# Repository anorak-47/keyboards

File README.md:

# keyboards
Handmade computer keyboards

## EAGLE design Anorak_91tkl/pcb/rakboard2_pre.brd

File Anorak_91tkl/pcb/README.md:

### The 91tkl: Another TKL keyboard PCB

A ten-key-less keyboard with ISO layout and three extra keys.

µCPU: AT90USB646 @ 16MHz

LED controller: 2x ISSI IS31FL3733

#### Notes for rev 2

Place diodes for keys "backspace" and "prtsc" on bottom of PCB

Use capacitors with a diameter below 4.5mm for C27, C26, C5, especially when putting them on the top side of the PCB.

The blue cathode pin of the LED for the key "pause" is not connected to anything. Connect it to the blue cathode pin of the LED for the key "scroll lock". 

#### Note: Out-of-the-box at90usb works only with external 8MHz crystal!

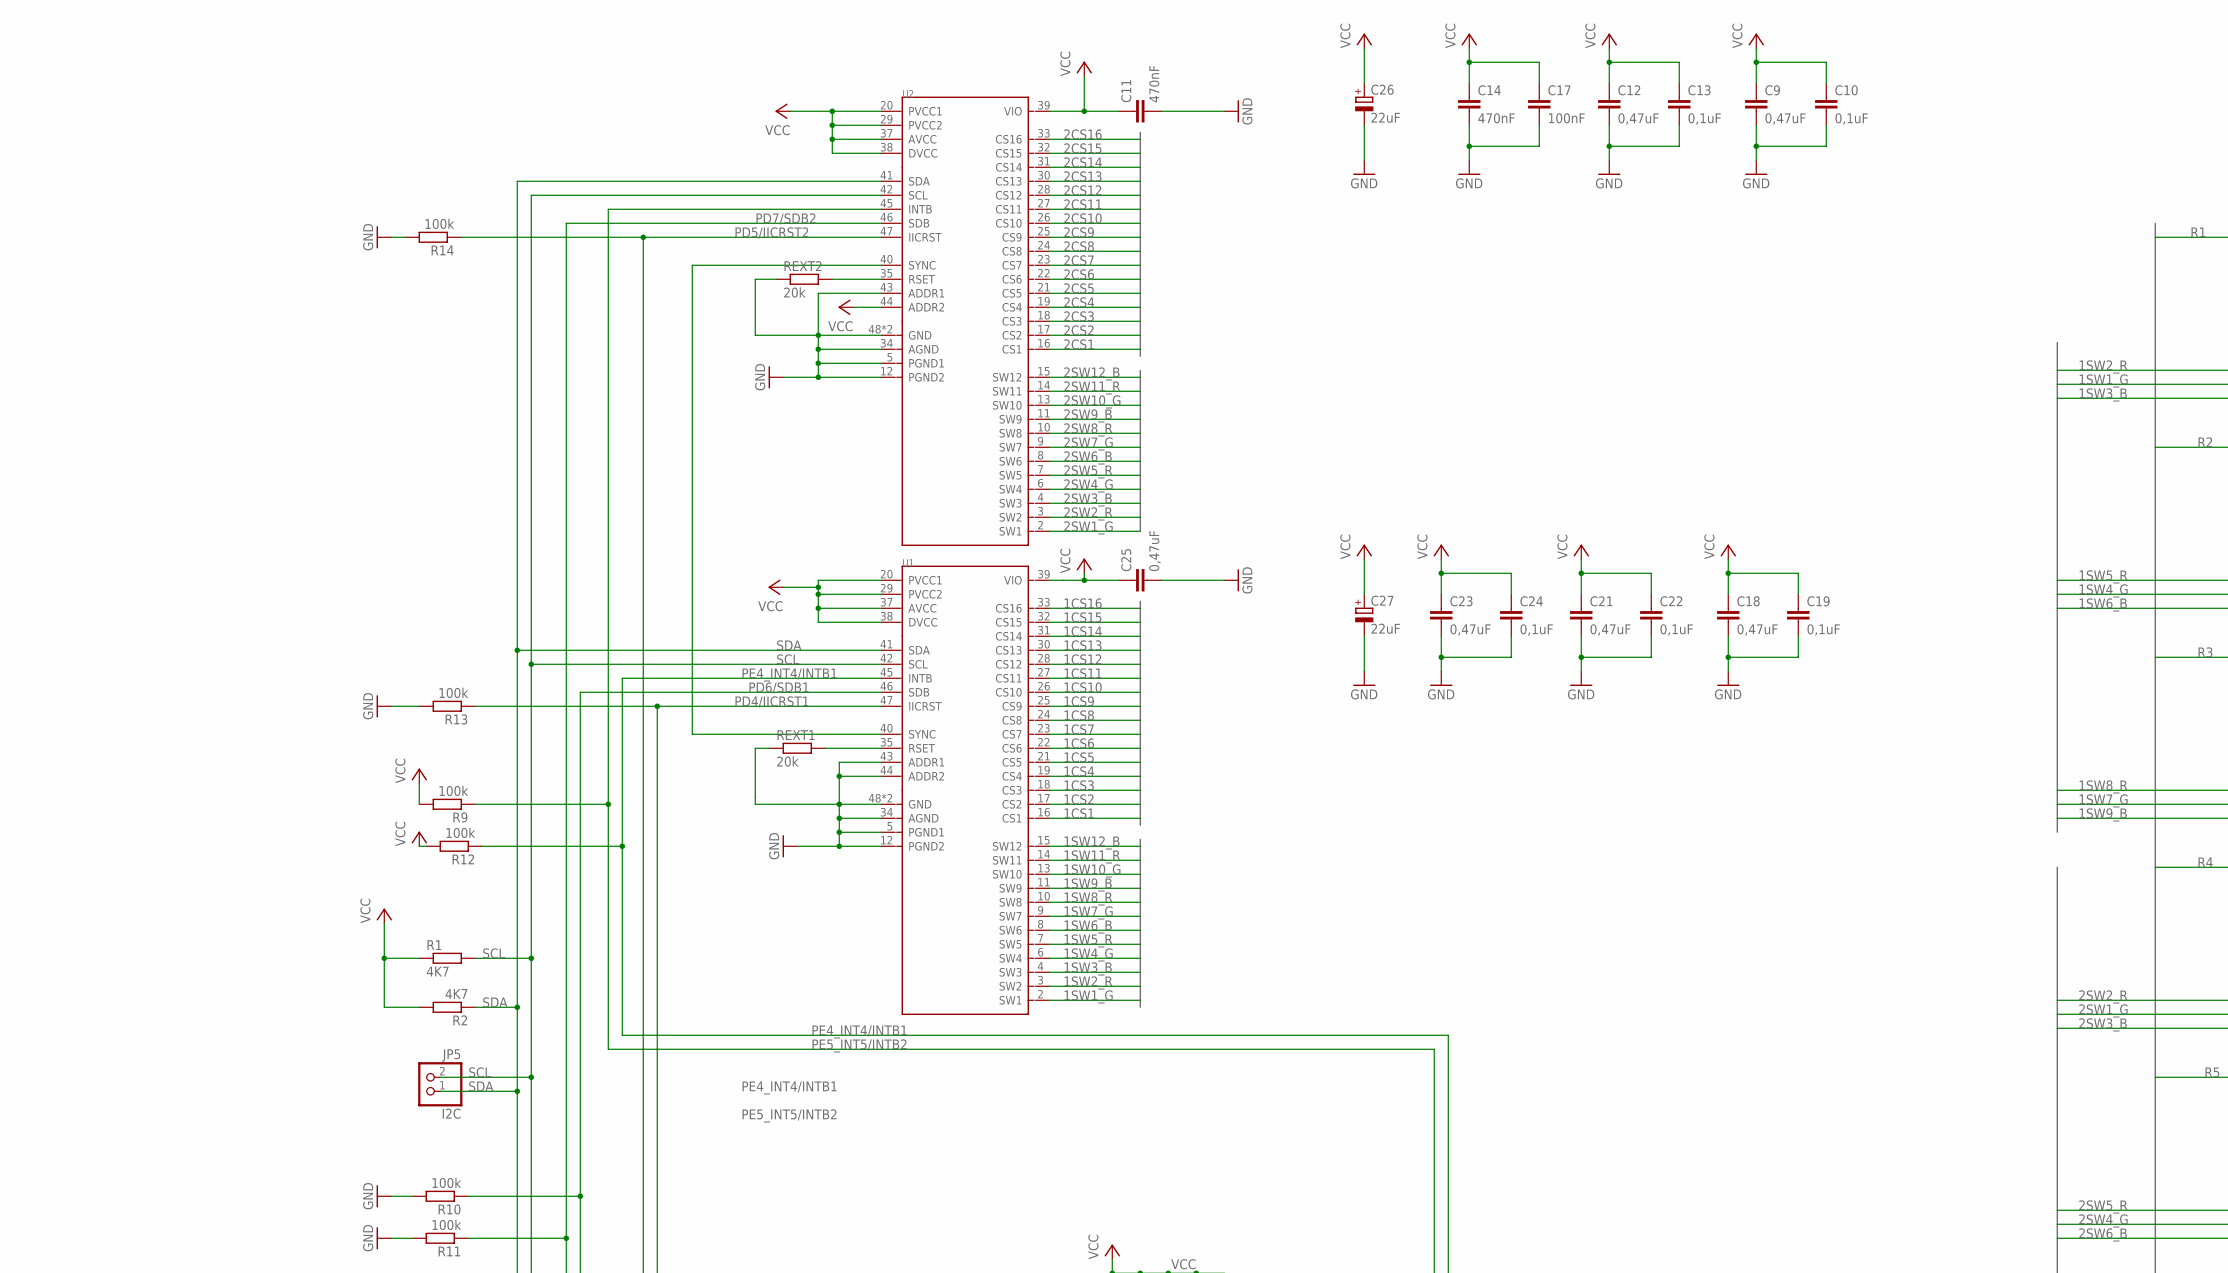
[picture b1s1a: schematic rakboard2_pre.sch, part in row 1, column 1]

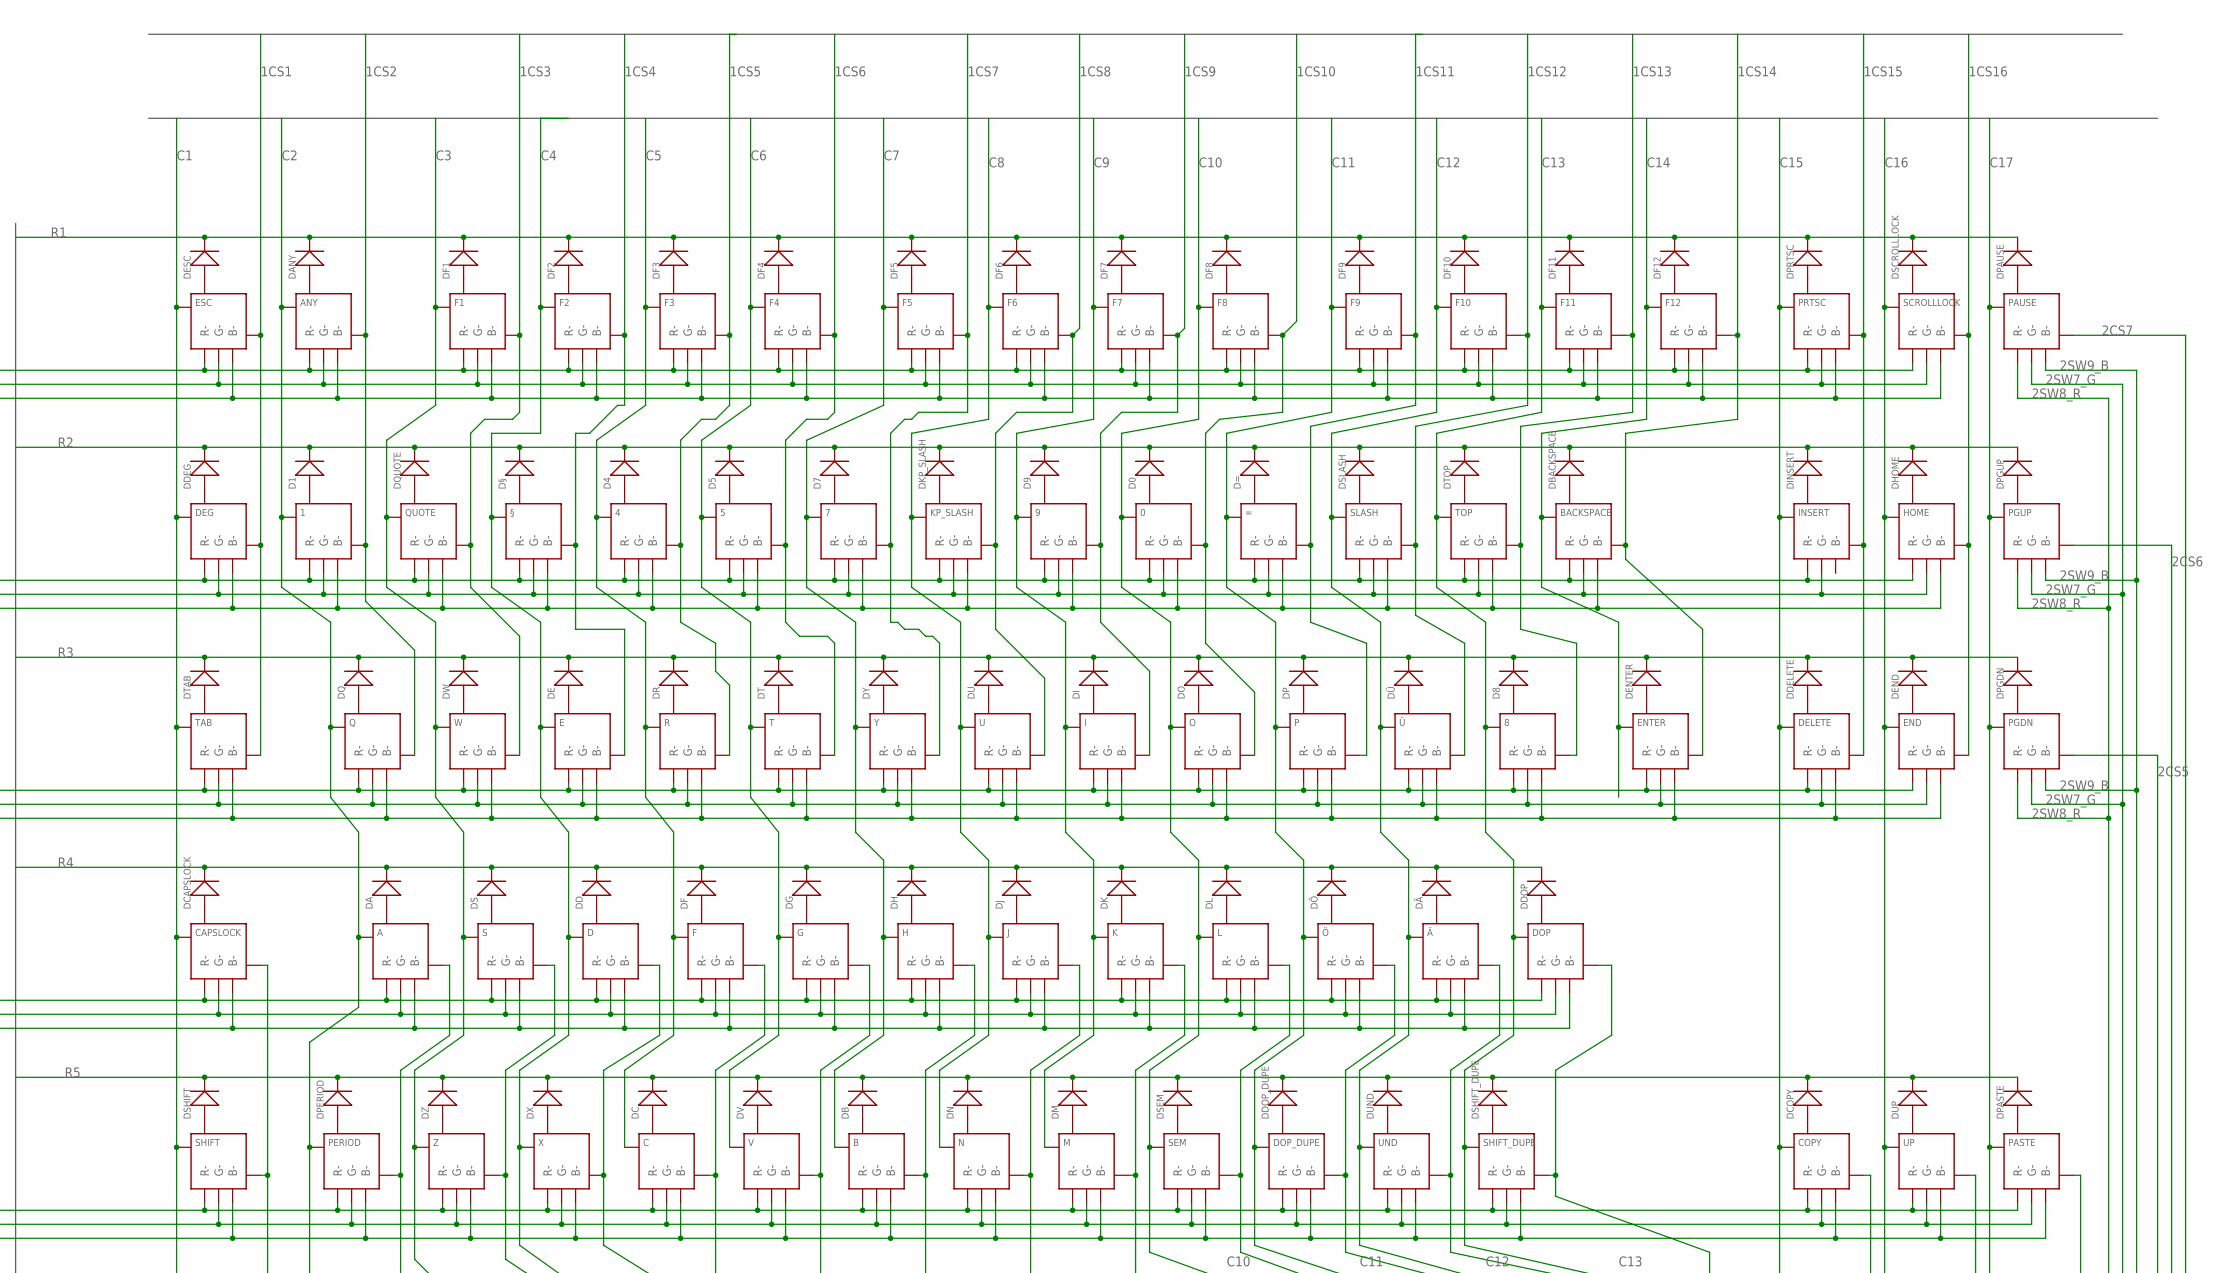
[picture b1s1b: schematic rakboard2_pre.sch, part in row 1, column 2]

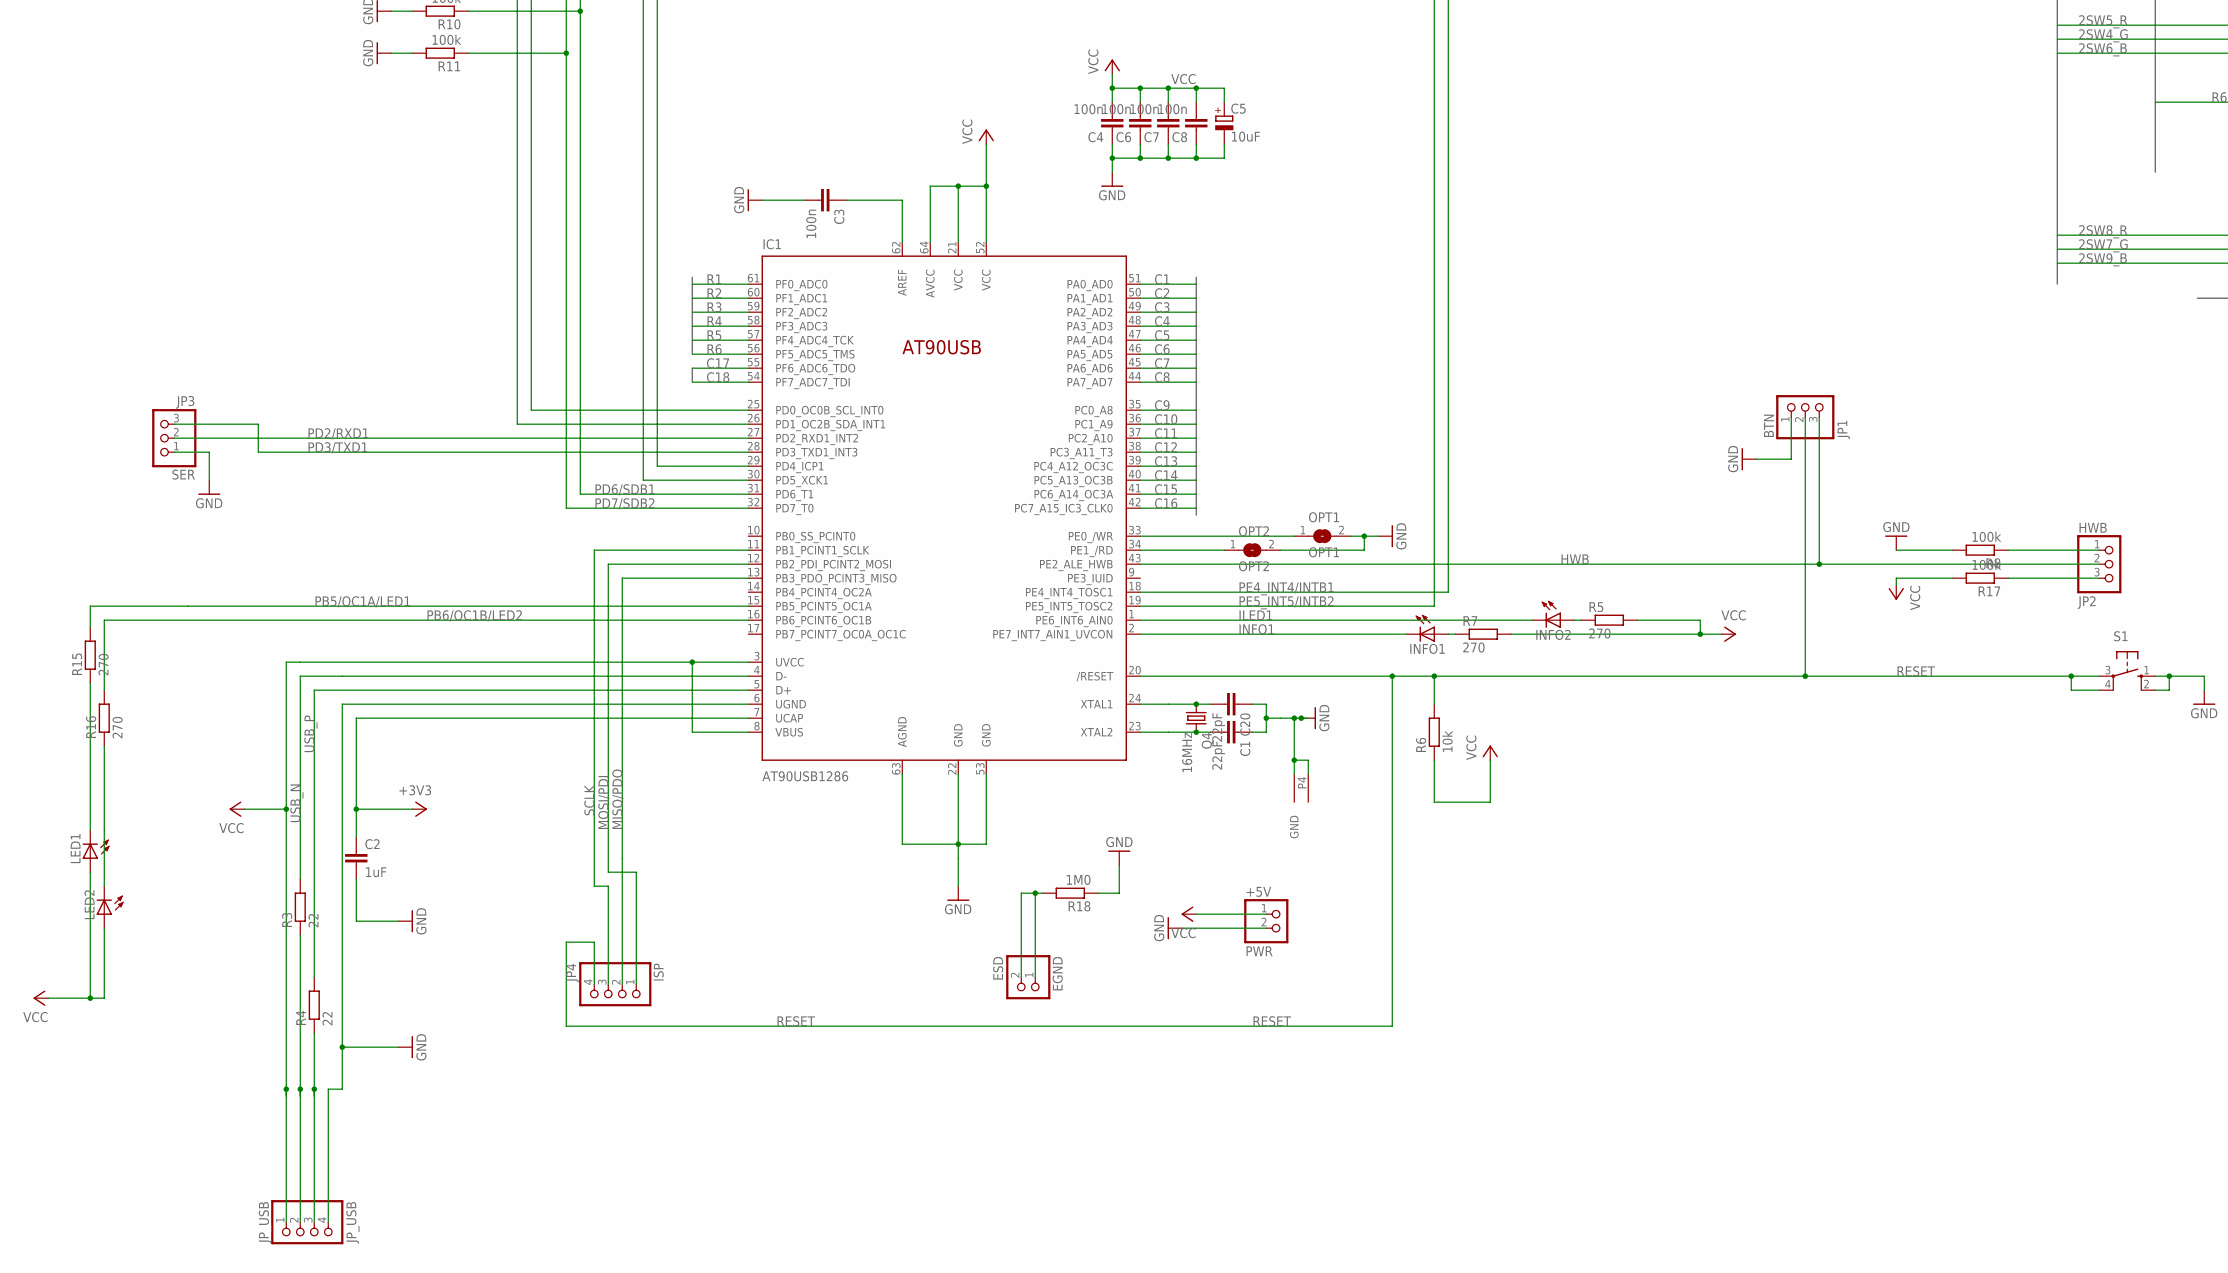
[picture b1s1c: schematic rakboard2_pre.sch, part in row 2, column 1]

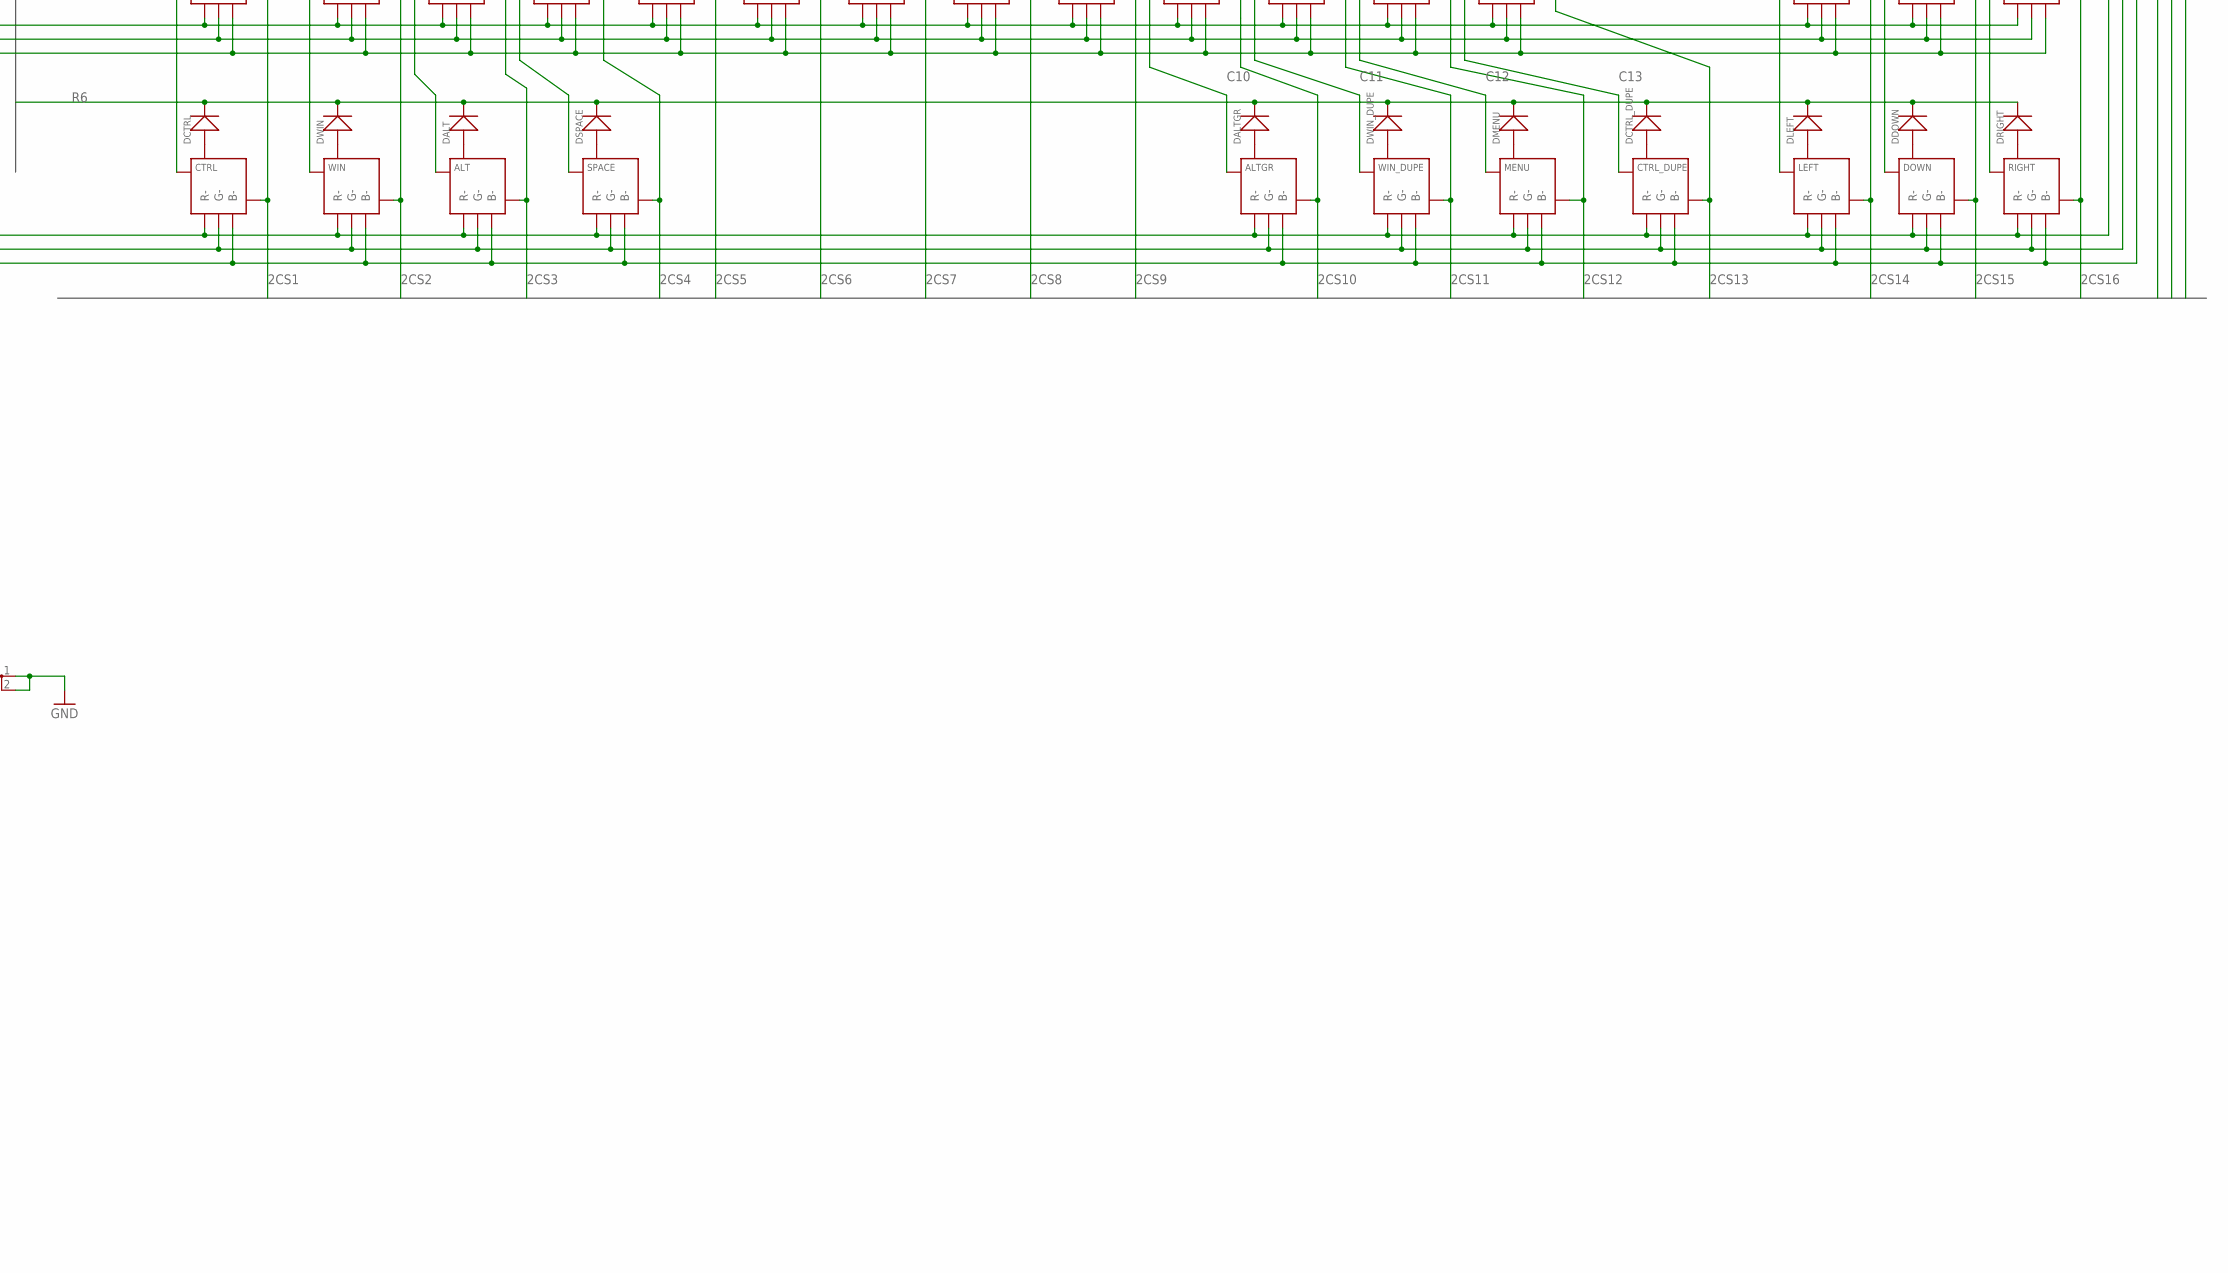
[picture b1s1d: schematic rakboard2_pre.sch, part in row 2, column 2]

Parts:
0, 1, 4, 5, 7, 8, 9: KEYSWITCH-RGBLED-ALPSMX-1U-RGB; ALPSMX-1U-RGB
+5V: PWR; 1X02
=: KEYSWITCH-RGBLED-ALPSMX-1U-RGB; ALPSMX-1U-RGB
A: KEYSWITCH-RGBLED-ALPSMX-1U-RGB; ALPSMX-1U-RGB
ALT: KEYSWITCH-RGBLED-ALPSMX-1U-RGB; ALPSMX-1U-RGB
ALTGR: KEYSWITCH-RGBLED-ALPSMX-1U-RGB; ALPSMX-1U-RGB
ANY: KEYSWITCH-RGBLED-ALPSMX-1U-RGB; ALPSMX-1U-RGB
B: KEYSWITCH-RGBLED-ALPSMX-1U-RGB; ALPSMX-1U-RGB
BACKSPACE: KEYSWITCH-RGBLED-ALPSMX-2U-RGB; ALPSMX-2U-RGB
BTN: JP1; 1X03
C: KEYSWITCH-RGBLED-ALPSMX-1U-RGB; ALPSMX-1U-RGB
C1, C20: 22pF; C1206
C2: 1uF; C1206
C3, C4, C6, C7, C8: 100n; C1206
C5: 10uF; E2-4
C9, C12, C18, C21, C23, C25: 0,47uF; C1206
C10, C13, C19, C22, C24: 0,1uF; C1206
C11, C14: 470nF; C1206
C17: 100nF; C1206
C26, C27: 22uF; E2-4
CAPSLOCK: KEYSWITCH-RGBLED-ALPSMX-1U-RGB; ALPSMX-1U-RGB
COPY: KEYSWITCH-RGBLED-ALPSMX-1U-RGB; ALPSMX-1U-RGB
CTRL: KEYSWITCH-RGBLED-ALPSMX-1U-RGB; ALPSMX-1U-RGB
CTRL_DUPE: KEYSWITCH-RGBLED-ALPSMX-1U-RGB; ALPSMX-1U-RGB
D: KEYSWITCH-RGBLED-ALPSMX-1U-RGB; ALPSMX-1U-RGB
D0, D1, D4, D5, D7, D8, D9: DIODE'1N4148'; DO-35
D=: DIODE'1N4148'; DO-35
DA: DIODE'1N4148'; DO-35
DALT: DIODE'1N4148'; DO-35
DALTGR: DIODE'1N4148'; DO-35
DANY: DIODE'1N4148'; DO-35
DB: DIODE'1N4148'; DO-35
DBACKSPACE: DIODE'1N4148'; DO-35
DC: DIODE'1N4148'; DO-35
DCAPSLOCK: DIODE'1N4148'; DO-35
DCOPY: DIODE'1N4148'; DO-35
DCTRL: DIODE'1N4148'; DO-35
DCTRL_DUPE: DIODE'1N4148'; DO-35
DD: DIODE'1N4148'; DO-35
DDEG: DIODE'1N4148'; DO-35
DDELETE: DIODE'1N4148'; DO-35
DDOP: DIODE'1N4148'; DO-35
DDOP_DUPE: DIODE'1N4148'; DO-35
DDOWN: DIODE'1N4148'; DO-35
DE: DIODE'1N4148'; DO-35
DEG: KEYSWITCH-RGBLED-ALPSMX-1U-RGB; ALPSMX-1U-RGB
DELETE: KEYSWITCH-RGBLED-ALPSMX-1U-RGB; ALPSMX-1U-RGB
DEND: DIODE'1N4148'; DO-35
DENTER: DIODE'1N4148'; DO-35
DESC: DIODE'1N4148'; DO-35
DF, DF1, DF2, DF3, DF4, DF5, DF6, DF7, DF8, DF9, DF10, DF11, DF12: DIODE'1N4148'; DO-35
DG: DIODE'1N4148'; DO-35
DH: DIODE'1N4148'; DO-35
DHOME: DIODE'1N4148'; DO-35
DI: DIODE'1N4148'; DO-35
DINSERT: DIODE'1N4148'; DO-35
DJ: DIODE'1N4148'; DO-35
DK: DIODE'1N4148'; DO-35
DKP_SLASH: DIODE'1N4148'; DO-35
DL: DIODE'1N4148'; DO-35
DLEFT: DIODE'1N4148'; DO-35
DM: DIODE'1N4148'; DO-35
DMENU: DIODE'1N4148'; DO-35
DN: DIODE'1N4148'; DO-35
DO: DIODE'1N4148'; DO-35
DOP: KEYSWITCH-RGBLED-ALPSMX-1U-RGB; ALPSMX-1U-RGB
DOP_DUPE: KEYSWITCH-RGBLED-ALPSMX-1U-RGB; ALPSMX-1U-RGB
DOWN: KEYSWITCH-RGBLED-ALPSMX-1U-RGB; ALPSMX-1U-RGB
DP: DIODE'1N4148'; DO-35
DPASTE: DIODE'1N4148'; DO-35
DPAUSE: DIODE'1N4148'; DO-35
DPERIOD: DIODE'1N4148'; DO-35
DPGDN: DIODE'1N4148'; DO-35
DPGUP: DIODE'1N4148'; DO-35
DPRTSC: DIODE'1N4148'; DO-35
DQ: DIODE'1N4148'; DO-35
DQUOTE: DIODE'1N4148'; DO-35
DR: DIODE'1N4148'; DO-35
DRIGHT: DIODE'1N4148'; DO-35
DS: DIODE'1N4148'; DO-35
DSCROLLLOCK: DIODE'1N4148'; DO-35
DSEM: DIODE'1N4148'; DO-35
DSHIFT: DIODE'1N4148'; DO-35
DSHIFT_DUPE: DIODE'1N4148'; DO-35
DSLASH: DIODE'1N4148'; DO-35
DSPACE: DIODE'1N4148'; DO-35
DT: DIODE'1N4148'; DO-35
DTAB: DIODE'1N4148'; DO-35
DTOP: DIODE'1N4148'; DO-35
DU: DIODE'1N4148'; DO-35
DUND: DIODE'1N4148'; DO-35
DUP: DIODE'1N4148'; DO-35
DV: DIODE'1N4148'; DO-35
DW: DIODE'1N4148'; DO-35
DWIN: DIODE'1N4148'; DO-35
DWIN_DUPE: DIODE'1N4148'; DO-35
DX: DIODE'1N4148'; DO-35
DY: DIODE'1N4148'; DO-35
DZ: DIODE'1N4148'; DO-35
D§: DIODE'1N4148'; DO-35
DÄ: DIODE'1N4148'; DO-35
DÖ: DIODE'1N4148'; DO-35
DÜ: DIODE'1N4148'; DO-35
E: KEYSWITCH-RGBLED-ALPSMX-1U-RGB; ALPSMX-1U-RGB
EGND: ESD; 1X02
END: KEYSWITCH-RGBLED-ALPSMX-1U-RGB; ALPSMX-1U-RGB
ENTER: KEYSWITCH-RGBLED-ALPSMX-2U-RGB; ALPSMX-2U-RGB
ESC: KEYSWITCH-RGBLED-ALPSMX-1U-RGB; ALPSMX-1U-RGB
F, F1, F2, F3, F4, F5, F6, F7, F8, F9, F10, F11, F12: KEYSWITCH-RGBLED-ALPSMX-1U-RGB; ALPSMX-1U-RGB
G: KEYSWITCH-RGBLED-ALPSMX-1U-RGB; ALPSMX-1U-RGB
H: KEYSWITCH-RGBLED-ALPSMX-1U-RGB; ALPSMX-1U-RGB
HOME: KEYSWITCH-RGBLED-ALPSMX-1U-RGB; ALPSMX-1U-RGB
HWB: JP2; 1X03
I: KEYSWITCH-RGBLED-ALPSMX-1U-RGB; ALPSMX-1U-RGB
I2C: JP5; 1X02
IC1: AT90USB1286; TQFP64
INFO1, INFO2: LEDSML0805; SML0805
INSERT: KEYSWITCH-RGBLED-ALPSMX-1U-RGB; ALPSMX-1U-RGB
ISP: JP4; 1X04
J: KEYSWITCH-RGBLED-ALPSMX-1U-RGB; ALPSMX-1U-RGB
JP_USB: JP_USB; 1X04
K: KEYSWITCH-RGBLED-ALPSMX-1U-RGB; ALPSMX-1U-RGB
KP_SLASH: KEYSWITCH-RGBLED-ALPSMX-1U-RGB; ALPSMX-1U-RGB
L: KEYSWITCH-RGBLED-ALPSMX-1U-RGB; ALPSMX-1U-RGB
LED1, LED2: LED3MM
LEFT: KEYSWITCH-RGBLED-ALPSMX-1U-RGB; ALPSMX-1U-RGB
M: KEYSWITCH-RGBLED-ALPSMX-1U-RGB; ALPSMX-1U-RGB
MENU: KEYSWITCH-RGBLED-ALPSMX-1U-RGB; ALPSMX-1U-RGB
N: KEYSWITCH-RGBLED-ALPSMX-1U-RGB; ALPSMX-1U-RGB
O: KEYSWITCH-RGBLED-ALPSMX-1U-RGB; ALPSMX-1U-RGB
OPT1: OPT1; SJ
OPT2: OPT2; SJ
P: KEYSWITCH-RGBLED-ALPSMX-1U-RGB; ALPSMX-1U-RGB
PASTE: KEYSWITCH-RGBLED-ALPSMX-1U-RGB; ALPSMX-1U-RGB
PAUSE: KEYSWITCH-RGBLED-ALPSMX-1U-RGB; ALPSMX-1U-RGB
PERIOD: KEYSWITCH-RGBLED-ALPSMX-1U-RGB; ALPSMX-1U-RGB
PGDN: KEYSWITCH-RGBLED-ALPSMX-1U-RGB; ALPSMX-1U-RGB
PGUP: KEYSWITCH-RGBLED-ALPSMX-1U-RGB; ALPSMX-1U-RGB
PRTSC: KEYSWITCH-RGBLED-ALPSMX-1U-RGB; ALPSMX-1U-RGB
Q: KEYSWITCH-RGBLED-ALPSMX-1U-RGB; ALPSMX-1U-RGB
Q4: 16MHz; MJ
QUOTE: KEYSWITCH-RGBLED-ALPSMX-1U-RGB; ALPSMX-1U-RGB
R: KEYSWITCH-RGBLED-ALPSMX-1U-RGB; ALPSMX-1U-RGB
R1, R2: 4K7; R1206
R3, R4: 22; R1206
R5, R7, R15, R16: 270; R1206
R6: 10k; R1206
R8, R9, R10, R11, R12, R13, R14, R17: 100k; R1206
R18: 1M0; R1206
REXT1, REXT2: 20k; R1206
RIGHT: KEYSWITCH-RGBLED-ALPSMX-1U-RGB; ALPSMX-1U-RGB
S: KEYSWITCH-RGBLED-ALPSMX-1U-RGB; ALPSMX-1U-RGB
S1: 10-XX; B3F-10XX
SCROLLLOCK: KEYSWITCH-RGBLED-ALPSMX-1U-RGB; ALPSMX-1U-RGB
SEM: KEYSWITCH-RGBLED-ALPSMX-1U-RGB; ALPSMX-1U-RGB
SER: JP3; 1X03
SHIFT: KEYSWITCH-RGBLED-ALPSMX-1U-RGB; ALPSMX-1U-RGB
SHIFT_DUPE: KEYSWITCH-RGBLED-ALPSMX-2U-RGB; ALPSMX-2U-RGB
SLASH: KEYSWITCH-RGBLED-ALPSMX-1U-RGB; ALPSMX-1U-RGB
SPACE: KEYSWITCH-RGBLED-ALPSMX-6.25U-RGB; ALPSMX-6.25U-RGB
T: KEYSWITCH-RGBLED-ALPSMX-1U-RGB; ALPSMX-1U-RGB
TAB: KEYSWITCH-RGBLED-ALPSMX-1U-RGB; ALPSMX-1U-RGB
TOP: KEYSWITCH-RGBLED-ALPSMX-1U-RGB; ALPSMX-1U-RGB
U: KEYSWITCH-RGBLED-ALPSMX-1U-RGB; ALPSMX-1U-RGB
U1, U2: IS31FL3733; LQFP48_7X7
UND: KEYSWITCH-RGBLED-ALPSMX-1U-RGB; ALPSMX-1U-RGB
UP: KEYSWITCH-RGBLED-ALPSMX-1U-RGB; ALPSMX-1U-RGB
V: KEYSWITCH-RGBLED-ALPSMX-1U-RGB; ALPSMX-1U-RGB
W: KEYSWITCH-RGBLED-ALPSMX-1U-RGB; ALPSMX-1U-RGB
WIN: KEYSWITCH-RGBLED-ALPSMX-1U-RGB; ALPSMX-1U-RGB
WIN_DUPE: KEYSWITCH-RGBLED-ALPSMX-1U-RGB; ALPSMX-1U-RGB
X: KEYSWITCH-RGBLED-ALPSMX-1U-RGB; ALPSMX-1U-RGB
Y: KEYSWITCH-RGBLED-ALPSMX-1U-RGB; ALPSMX-1U-RGB
Z: KEYSWITCH-RGBLED-ALPSMX-1U-RGB; ALPSMX-1U-RGB
§: KEYSWITCH-RGBLED-ALPSMX-1U-RGB; ALPSMX-1U-RGB
Ä: KEYSWITCH-RGBLED-ALPSMX-1U-RGB; ALPSMX-1U-RGB
Ö: KEYSWITCH-RGBLED-ALPSMX-1U-RGB; ALPSMX-1U-RGB
Ü: KEYSWITCH-RGBLED-ALPSMX-1U-RGB; ALPSMX-1U-RGB

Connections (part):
1CS1: DEG.LED+, ESC.LED+, TAB.LED+, U1.16 (CS1)
1CS2: 1.LED+, ANY.LED+, Q.LED+, U1.17 (CS2)
1CS3: F1.LED+, QUOTE.LED+, U1.18 (CS3), W.LED+
1CS4: E.LED+, F2.LED+, U1.19 (CS4), §.LED+
1CS5: 4.LED+, F3.LED+, R.LED+, U1.21 (CS5)
1CS6: 5.LED+, F4.LED+, T.LED+, U1.22 (CS6)
1CS7: 7.LED+, F5.LED+, U1.23 (CS7), Y.LED+
1CS8: F6.LED+, KP_SLASH.LED+, U.LED+, U1.24 (CS8)
1CS9: 9.LED+, F7.LED+, I.LED+, U1.25 (CS9)
1CS10: 0.LED+, F8.LED+, O.LED+, U1.26 (CS10)
1CS11: =.LED+, F9.LED+, P.LED+, U1.27 (CS11)
1CS12: F10.LED+, SLASH.LED+, U1.28 (CS12), Ü.LED+
1CS13: 8.LED+, F11.LED+, TOP.LED+, U1.30 (CS13)
1CS14: BACKSPACE.LED+, ENTER.LED+, F12.LED+, U1.31 (CS14)
1CS15: DELETE.LED+, INSERT.LED+, PRTSC.LED+, U1.32 (CS15)
1CS16: END.LED+, HOME.LED+, SCROLLLOCK.LED+, U1.33 (CS16)
1SW1_G: ANY.G-, ESC.G-, F1.G-, F2.G-, F3.G-, F4.G-, F5.G-, F6.G-, F7.G-, F8.G-, F9.G-, F10.G-, F11.G-, F12.G-, PRTSC.G-, SCROLLLOCK.G-, U1.2 (SW1)
1SW2_R: ANY.R-, ESC.R-, F1.R-, F2.R-, F3.R-, F4.R-, F5.R-, F6.R-, F7.R-, F8.R-, F9.R-, F10.R-, F11.R-, F12.R-, PRTSC.R-, SCROLLLOCK.R-, U1.3 (SW2)
1SW3_B: ANY.B-, ESC.B-, F1.B-, F2.B-, F3.B-, F4.B-, F5.B-, F6.B-, F7.B-, F8.B-, F9.B-, F10.B-, F11.B-, F12.B-, PRTSC.B-, SCROLLLOCK.B-, U1.4 (SW3)
1SW4_G: 0.G-, 1.G-, 4.G-, 5.G-, 7.G-, 9.G-, =.G-, BACKSPACE.G-, DEG.G-, HOME.G-, INSERT.G-, KP_SLASH.G-, QUOTE.G-, SLASH.G-, TOP.G-, U1.6 (SW4), §.G-
1SW5_R: 0.R-, 1.R-, 4.R-, 5.R-, 7.R-, 9.R-, =.R-, BACKSPACE.R-, DEG.R-, HOME.R-, INSERT.R-, KP_SLASH.R-, QUOTE.R-, SLASH.R-, TOP.R-, U1.7 (SW5), §.R-
1SW6_B: 0.B-, 1.B-, 4.B-, 5.B-, 7.B-, 9.B-, =.B-, BACKSPACE.B-, DEG.B-, HOME.B-, KP_SLASH.B-, QUOTE.B-, SLASH.B-, TOP.B-, U1.8 (SW6), §.B-
1SW7_G: 8.G-, DELETE.G-, E.G-, END.G-, ENTER.G-, I.G-, O.G-, P.G-, Q.G-, R.G-, T.G-, TAB.G-, U.G-, U1.9 (SW7), W.G-, Y.G-, Ü.G-
1SW8_R: 8.R-, DELETE.R-, E.R-, END.R-, ENTER.R-, I.R-, O.R-, P.R-, Q.R-, R.R-, T.R-, TAB.R-, U.R-, U1.10 (SW8), W.R-, Y.R-, Ü.R-
1SW9_B: 8.B-, DELETE.B-, E.B-, END.B-, ENTER.B-, I.B-, O.B-, P.B-, Q.B-, R.B-, T.B-, TAB.B-, U.B-, U1.11 (SW9), W.B-, Y.B-, Ü.B-
1SW10_G: U1.13 (SW10)
1SW11_R: U1.14 (SW11)
1SW12_B: U1.15 (SW12)
2CS1: CAPSLOCK.LED+, CTRL.LED+, SHIFT.LED+, U2.16 (CS1)
2CS2: A.LED+, PERIOD.LED+, U2.17 (CS2), WIN.LED+
2CS3: ALT.LED+, S.LED+, U2.18 (CS3), Z.LED+
2CS4: D.LED+, SPACE.LED+, U2.19 (CS4), X.LED+
2CS5: C.LED+, F.LED+, PGDN.LED+, U2.21 (CS5)
2CS6: G.LED+, PGUP.LED+, U2.22 (CS6), V.LED+
2CS7: B.LED+, H.LED+, PAUSE.LED+, U2.23 (CS7)
2CS8: J.LED+, N.LED+, U2.24 (CS8)
2CS9: K.LED+, M.LED+, U2.25 (CS9)
2CS10: ALTGR.LED+, L.LED+, SEM.LED+, U2.26 (CS10)
2CS11: DOP_DUPE.LED+, U2.27 (CS11), WIN_DUPE.LED+, Ö.LED+
2CS12: MENU.LED+, U2.28 (CS12), UND.LED+, Ä.LED+
2CS13: CTRL_DUPE.LED+, DOP.LED+, SHIFT_DUPE.LED+, U2.30 (CS13)
2CS14: COPY.LED+, LEFT.LED+, U2.31 (CS14)
2CS15: DOWN.LED+, U2.32 (CS15), UP.LED+
2CS16: PASTE.LED+, RIGHT.LED+, U2.33 (CS16)
2SW1_G: A.G-, CAPSLOCK.G-, D.G-, DOP.G-, F.G-, G.G-, H.G-, J.G-, K.G-, L.G-, S.G-, U2.2 (SW1), Ä.G-, Ö.G-
2SW2_R: A.R-, CAPSLOCK.R-, D.R-, DOP.R-, F.R-, G.R-, H.R-, J.R-, K.R-, L.R-, S.R-, U2.3 (SW2), Ä.R-, Ö.R-
2SW3_B: A.B-, CAPSLOCK.B-, D.B-, DOP.B-, F.B-, G.B-, H.B-, J.B-, K.B-, L.B-, S.B-, U2.4 (SW3), Ä.B-, Ö.B-
2SW4_G: B.G-, C.G-, COPY.G-, DOP_DUPE.G-, M.G-, N.G-, PASTE.G-, PERIOD.G-, SEM.G-, SHIFT.G-, SHIFT_DUPE.G-, U2.6 (SW4), UND.G-, UP.G-, V.G-, X.G-, Z.G-
2SW5_R: B.R-, C.R-, COPY.R-, DOP_DUPE.R-, M.R-, N.R-, PASTE.R-, PERIOD.R-, SEM.R-, SHIFT.R-, SHIFT_DUPE.R-, U2.7 (SW5), UND.R-, UP.R-, V.R-, X.R-, Z.R-
2SW6_B: B.B-, C.B-, COPY.B-, DOP_DUPE.B-, M.B-, N.B-, PASTE.B-, PERIOD.B-, SEM.B-, SHIFT.B-, SHIFT_DUPE.B-, U2.8 (SW6), UND.B-, UP.B-, V.B-, X.B-, Z.B-
2SW7_G: ALT.G-, ALTGR.G-, CTRL.G-, CTRL_DUPE.G-, DOWN.G-, LEFT.G-, MENU.G-, PAUSE.G-, PGDN.G-, PGUP.G-, RIGHT.G-, SPACE.G-, U2.9 (SW7), WIN.G-, WIN_DUPE.G-
2SW8_R: ALT.R-, ALTGR.R-, CTRL.R-, CTRL_DUPE.R-, DOWN.R-, LEFT.R-, MENU.R-, PAUSE.R-, PGDN.R-, PGUP.R-, RIGHT.R-, SPACE.R-, U2.10 (SW8), WIN.R-, WIN_DUPE.R-
2SW9_B: ALT.B-, ALTGR.B-, CTRL.B-, CTRL_DUPE.B-, DOWN.B-, LEFT.B-, MENU.B-, PAUSE.B-, PGDN.B-, PGUP.B-, RIGHT.B-, SPACE.B-, U2.11 (SW9), WIN.B-, WIN_DUPE.B-
2SW10_G: U2.13 (SW10)
2SW11_R: U2.14 (SW11)
2SW12_B: U2.15 (SW12)
+3V3: C2.1, IC1.7 (UCAP)
C1: CAPSLOCK.ALPS1 (P0), CAPSLOCK.MX1 (P0), CTRL.ALPS1 (P0), CTRL.MX1 (P0), DEG.ALPS1 (P0), DEG.MX1 (P0), ESC.ALPS1 (P0), ESC.MX1 (P0), IC1.51 (PA0_AD0), SHIFT.ALPS1 (P0), SHIFT.MX1 (P0), TAB.ALPS1 (P0), TAB.MX1 (P0)
C2: 1.ALPS1 (P0), 1.MX1 (P0), A.ALPS1 (P0), A.MX1 (P0), ANY.ALPS1 (P0), ANY.MX1 (P0), IC1.50 (PA1_AD1), PERIOD.ALPS1 (P0), PERIOD.MX1 (P0), Q.ALPS1 (P0), Q.MX1 (P0), WIN.ALPS1 (P0), WIN.MX1 (P0)
C3: ALT.ALPS1 (P0), ALT.MX1 (P0), F1.ALPS1 (P0), F1.MX1 (P0), IC1.49 (PA2_AD2), QUOTE.ALPS1 (P0), QUOTE.MX1 (P0), S.ALPS1 (P0), S.MX1 (P0), W.ALPS1 (P0), W.MX1 (P0), Z.ALPS1 (P0), Z.MX1 (P0)
C4: D.ALPS1 (P0), D.MX1 (P0), E.ALPS1 (P0), E.MX1 (P0), F2.ALPS1 (P0), F2.MX1 (P0), IC1.48 (PA3_AD3), SPACE.ALPS1 (P0), SPACE.MX1 (P0), X.ALPS1 (P0), X.MX1 (P0), §.ALPS1 (P0), §.MX1 (P0)
C5: 4.ALPS1 (P0), 4.MX1 (P0), C.ALPS1 (P0), C.MX1 (P0), F.ALPS1 (P0), F.MX1 (P0), F3.ALPS1 (P0), F3.MX1 (P0), IC1.47 (PA4_AD4), R.ALPS1 (P0), R.MX1 (P0)
C6: 5.ALPS1 (P0), 5.MX1 (P0), F4.ALPS1 (P0), F4.MX1 (P0), G.ALPS1 (P0), G.MX1 (P0), IC1.46 (PA5_AD5), T.ALPS1 (P0), T.MX1 (P0), V.ALPS1 (P0), V.MX1 (P0)
C7: 7.ALPS1 (P0), 7.MX1 (P0), B.ALPS1 (P0), B.MX1 (P0), F5.ALPS1 (P0), F5.MX1 (P0), H.ALPS1 (P0), H.MX1 (P0), IC1.45 (PA6_AD6), Y.ALPS1 (P0), Y.MX1 (P0)
C8: F6.ALPS1 (P0), F6.MX1 (P0), IC1.44 (PA7_AD7), J.ALPS1 (P0), J.MX1 (P0), KP_SLASH.ALPS1 (P0), KP_SLASH.MX1 (P0), N.ALPS1 (P0), N.MX1 (P0), U.ALPS1 (P0), U.MX1 (P0)
C9: 9.ALPS1 (P0), 9.MX1 (P0), F7.ALPS1 (P0), F7.MX1 (P0), I.ALPS1 (P0), I.MX1 (P0), IC1.35 (PC0_A8), K.ALPS1 (P0), K.MX1 (P0), M.ALPS1 (P0), M.MX1 (P0)
C10: 0.ALPS1 (P0), 0.MX1 (P0), ALTGR.ALPS1 (P0), ALTGR.MX1 (P0), F8.ALPS1 (P0), F8.MX1 (P0), IC1.36 (PC1_A9), L.ALPS1 (P0), L.MX1 (P0), O.ALPS1 (P0), O.MX1 (P0), SEM.ALPS1 (P0), SEM.MX1 (P0)
C11: =.ALPS1 (P0), =.MX1 (P0), DOP_DUPE.ALPS1 (P0), DOP_DUPE.MX1 (P0), F9.ALPS1 (P0), F9.MX1 (P0), IC1.37 (PC2_A10), P.ALPS1 (P0), P.MX1 (P0), WIN_DUPE.ALPS1 (P0), WIN_DUPE.MX1 (P0), Ö.ALPS1 (P0), Ö.MX1 (P0)
C12: F10.ALPS1 (P0), F10.MX1 (P0), IC1.38 (PC3_A11_T3), MENU.ALPS1 (P0), MENU.MX1 (P0), SLASH.ALPS1 (P0), SLASH.MX1 (P0), UND.ALPS1 (P0), UND.MX1 (P0), Ä.ALPS1 (P0), Ä.MX1 (P0), Ü.ALPS1 (P0), Ü.MX1 (P0)
C13: 8.ALPS1 (P0), 8.MX1 (P0), CTRL_DUPE.ALPS1 (P0), CTRL_DUPE.MX1 (P0), DOP.ALPS1 (P0), DOP.MX1 (P0), F11.ALPS1 (P0), F11.MX1 (P0), IC1.39 (PC4_A12_OC3C), SHIFT_DUPE.ALPS1 (P0), SHIFT_DUPE.MX1 (P0), TOP.ALPS1 (P0), TOP.MX1 (P0)
C14: BACKSPACE.ALPS1 (P0), BACKSPACE.MX1 (P0), ENTER.ALPS1 (P0), ENTER.MX1 (P0), F12.ALPS1 (P0), F12.MX1 (P0), IC1.40 (PC5_A13_OC3B)
C15: COPY.ALPS1 (P0), COPY.MX1 (P0), DELETE.ALPS1 (P0), DELETE.MX1 (P0), IC1.41 (PC6_A14_OC3A), INSERT.ALPS1 (P0), INSERT.MX1 (P0), LEFT.ALPS1 (P0), LEFT.MX1 (P0), PRTSC.ALPS1 (P0), PRTSC.MX1 (P0)
C16: DOWN.ALPS1 (P0), DOWN.MX1 (P0), END.ALPS1 (P0), END.MX1 (P0), HOME.ALPS1 (P0), HOME.MX1 (P0), IC1.42 (PC7_A15_IC3_CLK0), SCROLLLOCK.ALPS1 (P0), SCROLLLOCK.MX1 (P0), UP.ALPS1 (P0), UP.MX1 (P0)
C17: IC1.55 (PF6_ADC6_TDO), PASTE.ALPS1 (P0), PASTE.MX1 (P0), PAUSE.ALPS1 (P0), PAUSE.MX1 (P0), PGDN.ALPS1 (P0), PGDN.MX1 (P0), PGUP.ALPS1 (P0), PGUP.MX1 (P0), RIGHT.ALPS1 (P0), RIGHT.MX1 (P0)
C18: IC1.54 (PF7_ADC7_TDI)
GND: +5V.2, BTN.1, C1.1, C2.2, C3.2, C4.1, C5.-, C6.1, C7.1, C8.1, C9.2, C10.2, C11.2, C12.2, C13.2, C14.2, C17.2, C18.2, C19.2, C20.1, C21.2, C22.2, C23.2, C24.2, C25.2, C26.-, C27.-, IC1.6 (UGND), IC1.22 (GND), IC1.53 (GND), IC1.63 (AGND), JP_USB.4, OPT1.2, OPT2.2, Q4.P2 (GND), Q4.P4 (GND1), R8.2, R10.2, R11.2, R13.2, R14.2, R18.1, REXT1.1, REXT2.1, S1.1 (S), S1.2 (S1), SER.1, U1.5 (PGND1), U1.12 (PGND2), U1.34 (AGND), U1.43 (ADDR1), U1.44 (ADDR2), U1.48 (GND), U1.TP (GND), U2.5 (PGND1), U2.12 (PGND2), U2.34 (AGND), U2.43 (ADDR1), U2.48 (GND), U2.TP (GND)
HWB: BTN.3, HWB.2, IC1.43 (PE2_ALE_HWB)
ILED1: IC1.1 (PE6_INT6_AIN0), INFO2.C
INFO1: IC1.2 (PE7_INT7_AIN1_UVCON), INFO1.C
ISSI_SYNC: U1.40 (SYNC), U2.40 (SYNC)
MISO/PDO: IC1.13 (PB3_PDO_PCINT3_MISO), ISP.2
MOSI/PDI: IC1.12 (PB2_PDI_PCINT2_MOSI), ISP.1
unnamed: DESC.A (+), ESC.ALPS2 (P1), ESC.MX2 (P1)
unnamed: INFO1.A, R7.1
unnamed: REXT1.2, U1.35 (RSET)
unnamed: REXT2.2, U2.35 (RSET)
unnamed: HWB.1, R8.1
unnamed: EGND.1, EGND.2, R18.2
unnamed: ANY.ALPS2 (P1), ANY.MX2 (P1), DANY.A (+)
unnamed: DF1.A (+), F1.ALPS2 (P1), F1.MX2 (P1)
unnamed: DF2.A (+), F2.ALPS2 (P1), F2.MX2 (P1)
unnamed: DF3.A (+), F3.ALPS2 (P1), F3.MX2 (P1)
unnamed: DF4.A (+), F4.ALPS2 (P1), F4.MX2 (P1)
unnamed: DF5.A (+), F5.ALPS2 (P1), F5.MX2 (P1)
unnamed: DF6.A (+), F6.ALPS2 (P1), F6.MX2 (P1)
unnamed: DF7.A (+), F7.ALPS2 (P1), F7.MX2 (P1)
unnamed: DF8.A (+), F8.ALPS2 (P1), F8.MX2 (P1)
unnamed: DF9.A (+), F9.ALPS2 (P1), F9.MX2 (P1)
unnamed: DF10.A (+), F10.ALPS2 (P1), F10.MX2 (P1)
unnamed: DF11.A (+), F11.ALPS2 (P1), F11.MX2 (P1)
unnamed: HWB.3, R17.1
unnamed: C3.1, IC1.62 (AREF)
unnamed: DF12.A (+), F12.ALPS2 (P1), F12.MX2 (P1)
unnamed: DPRTSC.A (+), PRTSC.ALPS2 (P1), PRTSC.MX2 (P1)
unnamed: DSCROLLLOCK.A (+), SCROLLLOCK.ALPS2 (P1), SCROLLLOCK.MX2 (P1)
unnamed: DPAUSE.A (+), PAUSE.ALPS2 (P1), PAUSE.MX2 (P1)
unnamed: DDEG.A (+), DEG.ALPS2 (P1), DEG.MX2 (P1)
unnamed: 1.ALPS2 (P1), 1.MX2 (P1), D1.A (+)
unnamed: DQUOTE.A (+), QUOTE.ALPS2 (P1), QUOTE.MX2 (P1)
unnamed: D§.A (+), §.ALPS2 (P1), §.MX2 (P1)
unnamed: 4.ALPS2 (P1), 4.MX2 (P1), D4.A (+)
unnamed: 5.ALPS2 (P1), 5.MX2 (P1), D5.A (+)
unnamed: 7.ALPS2 (P1), 7.MX2 (P1), D7.A (+)
unnamed: IC1.33 (PE0_/WR), OPT1.1
unnamed: DKP_SLASH.A (+), KP_SLASH.ALPS2 (P1), KP_SLASH.MX2 (P1)
unnamed: IC1.34 (PE1_/RD), OPT2.1
unnamed: 9.ALPS2 (P1), 9.MX2 (P1), D9.A (+)
unnamed: 0.ALPS2 (P1), 0.MX2 (P1), D0.A (+)
unnamed: =.ALPS2 (P1), =.MX2 (P1), D=.A (+)
unnamed: INFO2.A, R5.1
unnamed: DSLASH.A (+), SLASH.ALPS2 (P1), SLASH.MX2 (P1)
unnamed: DTOP.A (+), TOP.ALPS2 (P1), TOP.MX2 (P1)
unnamed: BACKSPACE.ALPS2 (P1), BACKSPACE.MX2 (P1), DBACKSPACE.A (+)
unnamed: DINSERT.A (+), INSERT.ALPS2 (P1), INSERT.MX2 (P1)
unnamed: DHOME.A (+), HOME.ALPS2 (P1), HOME.MX2 (P1)
unnamed: DPGUP.A (+), PGUP.ALPS2 (P1), PGUP.MX2 (P1)
unnamed: DTAB.A (+), TAB.ALPS2 (P1), TAB.MX2 (P1)
unnamed: DQ.A (+), Q.ALPS2 (P1), Q.MX2 (P1)
unnamed: DW.A (+), W.ALPS2 (P1), W.MX2 (P1)
unnamed: DE.A (+), E.ALPS2 (P1), E.MX2 (P1)
unnamed: DR.A (+), R.ALPS2 (P1), R.MX2 (P1)
unnamed: DT.A (+), T.ALPS2 (P1), T.MX2 (P1)
unnamed: DY.A (+), Y.ALPS2 (P1), Y.MX2 (P1)
unnamed: DU.A (+), U.ALPS2 (P1), U.MX2 (P1)
unnamed: DI.A (+), I.ALPS2 (P1), I.MX2 (P1)
unnamed: DO.A (+), O.ALPS2 (P1), O.MX2 (P1)
unnamed: DP.A (+), P.ALPS2 (P1), P.MX2 (P1)
unnamed: C1.2, IC1.23 (XTAL2), Q4.P3 (2)
unnamed: C20.2, IC1.24 (XTAL1), Q4.P1 (1)
unnamed: DÜ.A (+), Ü.ALPS2 (P1), Ü.MX2 (P1)
unnamed: LED1.K (C), R15.1
unnamed: LED2.K (C), R16.1
unnamed: 8.ALPS2 (P1), 8.MX2 (P1), D8.A (+)
unnamed: DENTER.A (+), ENTER.ALPS2 (P1), ENTER.MX2 (P1)
unnamed: DDELETE.A (+), DELETE.ALPS2 (P1), DELETE.MX2 (P1)
unnamed: DEND.A (+), END.ALPS2 (P1), END.MX2 (P1)
unnamed: DPGDN.A (+), PGDN.ALPS2 (P1), PGDN.MX2 (P1)
unnamed: CAPSLOCK.ALPS2 (P1), CAPSLOCK.MX2 (P1), DCAPSLOCK.A (+)
unnamed: A.ALPS2 (P1), A.MX2 (P1), DA.A (+)
unnamed: DS.A (+), S.ALPS2 (P1), S.MX2 (P1)
unnamed: D.ALPS2 (P1), D.MX2 (P1), DD.A (+)
unnamed: DF.A (+), F.ALPS2 (P1), F.MX2 (P1)
unnamed: DG.A (+), G.ALPS2 (P1), G.MX2 (P1)
unnamed: DH.A (+), H.ALPS2 (P1), H.MX2 (P1)
unnamed: DJ.A (+), J.ALPS2 (P1), J.MX2 (P1)
unnamed: DK.A (+), K.ALPS2 (P1), K.MX2 (P1)
unnamed: DL.A (+), L.ALPS2 (P1), L.MX2 (P1)
unnamed: DÖ.A (+), Ö.ALPS2 (P1), Ö.MX2 (P1)
unnamed: DÄ.A (+), Ä.ALPS2 (P1), Ä.MX2 (P1)
unnamed: DDOP.A (+), DOP.ALPS2 (P1), DOP.MX2 (P1)
unnamed: DSHIFT.A (+), SHIFT.ALPS2 (P1), SHIFT.MX2 (P1)
unnamed: DPERIOD.A (+), PERIOD.ALPS2 (P1), PERIOD.MX2 (P1)
unnamed: DZ.A (+), Z.ALPS2 (P1), Z.MX2 (P1)
unnamed: DX.A (+), X.ALPS2 (P1), X.MX2 (P1)
unnamed: C.ALPS2 (P1), C.MX2 (P1), DC.A (+)
unnamed: DV.A (+), V.ALPS2 (P1), V.MX2 (P1)
unnamed: B.ALPS2 (P1), B.MX2 (P1), DB.A (+)
unnamed: DN.A (+), N.ALPS2 (P1), N.MX2 (P1)
unnamed: DM.A (+), M.ALPS2 (P1), M.MX2 (P1)
unnamed: DSEM.A (+), SEM.ALPS2 (P1), SEM.MX2 (P1)
unnamed: DDOP_DUPE.A (+), DOP_DUPE.ALPS2 (P1), DOP_DUPE.MX2 (P1)
unnamed: DUND.A (+), UND.ALPS2 (P1), UND.MX2 (P1)
unnamed: DSHIFT_DUPE.A (+), SHIFT_DUPE.ALPS2 (P1), SHIFT_DUPE.MX2 (P1)
unnamed: COPY.ALPS2 (P1), COPY.MX2 (P1), DCOPY.A (+)
unnamed: DUP.A (+), UP.ALPS2 (P1), UP.MX2 (P1)
unnamed: DPASTE.A (+), PASTE.ALPS2 (P1), PASTE.MX2 (P1)
unnamed: CTRL.ALPS2 (P1), CTRL.MX2 (P1), DCTRL.A (+)
unnamed: DWIN.A (+), WIN.ALPS2 (P1), WIN.MX2 (P1)
unnamed: ALT.ALPS2 (P1), ALT.MX2 (P1), DALT.A (+)
unnamed: DSPACE.A (+), SPACE.ALPS2 (P1), SPACE.MX2 (P1)
unnamed: ALTGR.ALPS2 (P1), ALTGR.MX2 (P1), DALTGR.A (+)
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

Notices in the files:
parts and their libraries:
SparkFun-Connectors: Licensing: CC v3.0 Share-Alike You are welcome to use this library for commercial purposes.
eagle-library-edeca.net-v5: This is v1 and is licensed under the Creative Commons (Attribution-Non-Commercial-Share Alike 2.0 UK)
